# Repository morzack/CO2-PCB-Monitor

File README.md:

# CO2-PCB-Monitor

## v1

This repo contains the hardware and software required to manufacture and assemble a small seven segment CO2 monitor.

The monitor is built around a 4 digit seven segment display (with automatic dimming based on ambient light) that displays the current atmospheric CO2 concentration as measured by an Adafruit SCD-40 module over i2c.

In practice, this project can serve as a generic platform for any i2c module that might benefit from a 4 digit display. Potentially, other projects could be built around this architecture.

There is a BOM included: the total cost per unit, as of when it was made in early 2025, was ~90 USD.
Most of the cost comes from the SCD-40 module used -- directly integrating one of the modules onto the board should lower that price.

A rough block diagram is below:

The system has two power domains: a 5V domain is used for all digital logic, while the 3V domain is reserved for the seven-segement characters and associated dimming circuit.
This separation of power supplies was chosen to both allow for a soft startup sequence (putting less strain on the overall power supply), and to remove some voltage headroom for the LEDs.

The final design was manufactured using JLCPCB's services. A BOM is included with this repo, as well as manufacturing files.

The board can be programmed using the Arduino IDE and a separate ISP over the SPI lines.

## v2

Following the success of the first version, I want to make a few changes to ease manufacturing.
In particular, the design should shift to SMT where possible to enable JLCPCB PCBA.

The SPI and UART headers can be rethought as well to allow for future off-board additions.
There's value in making a port that an ESP32 or similar SoC can clip into for periodic recording over a network.

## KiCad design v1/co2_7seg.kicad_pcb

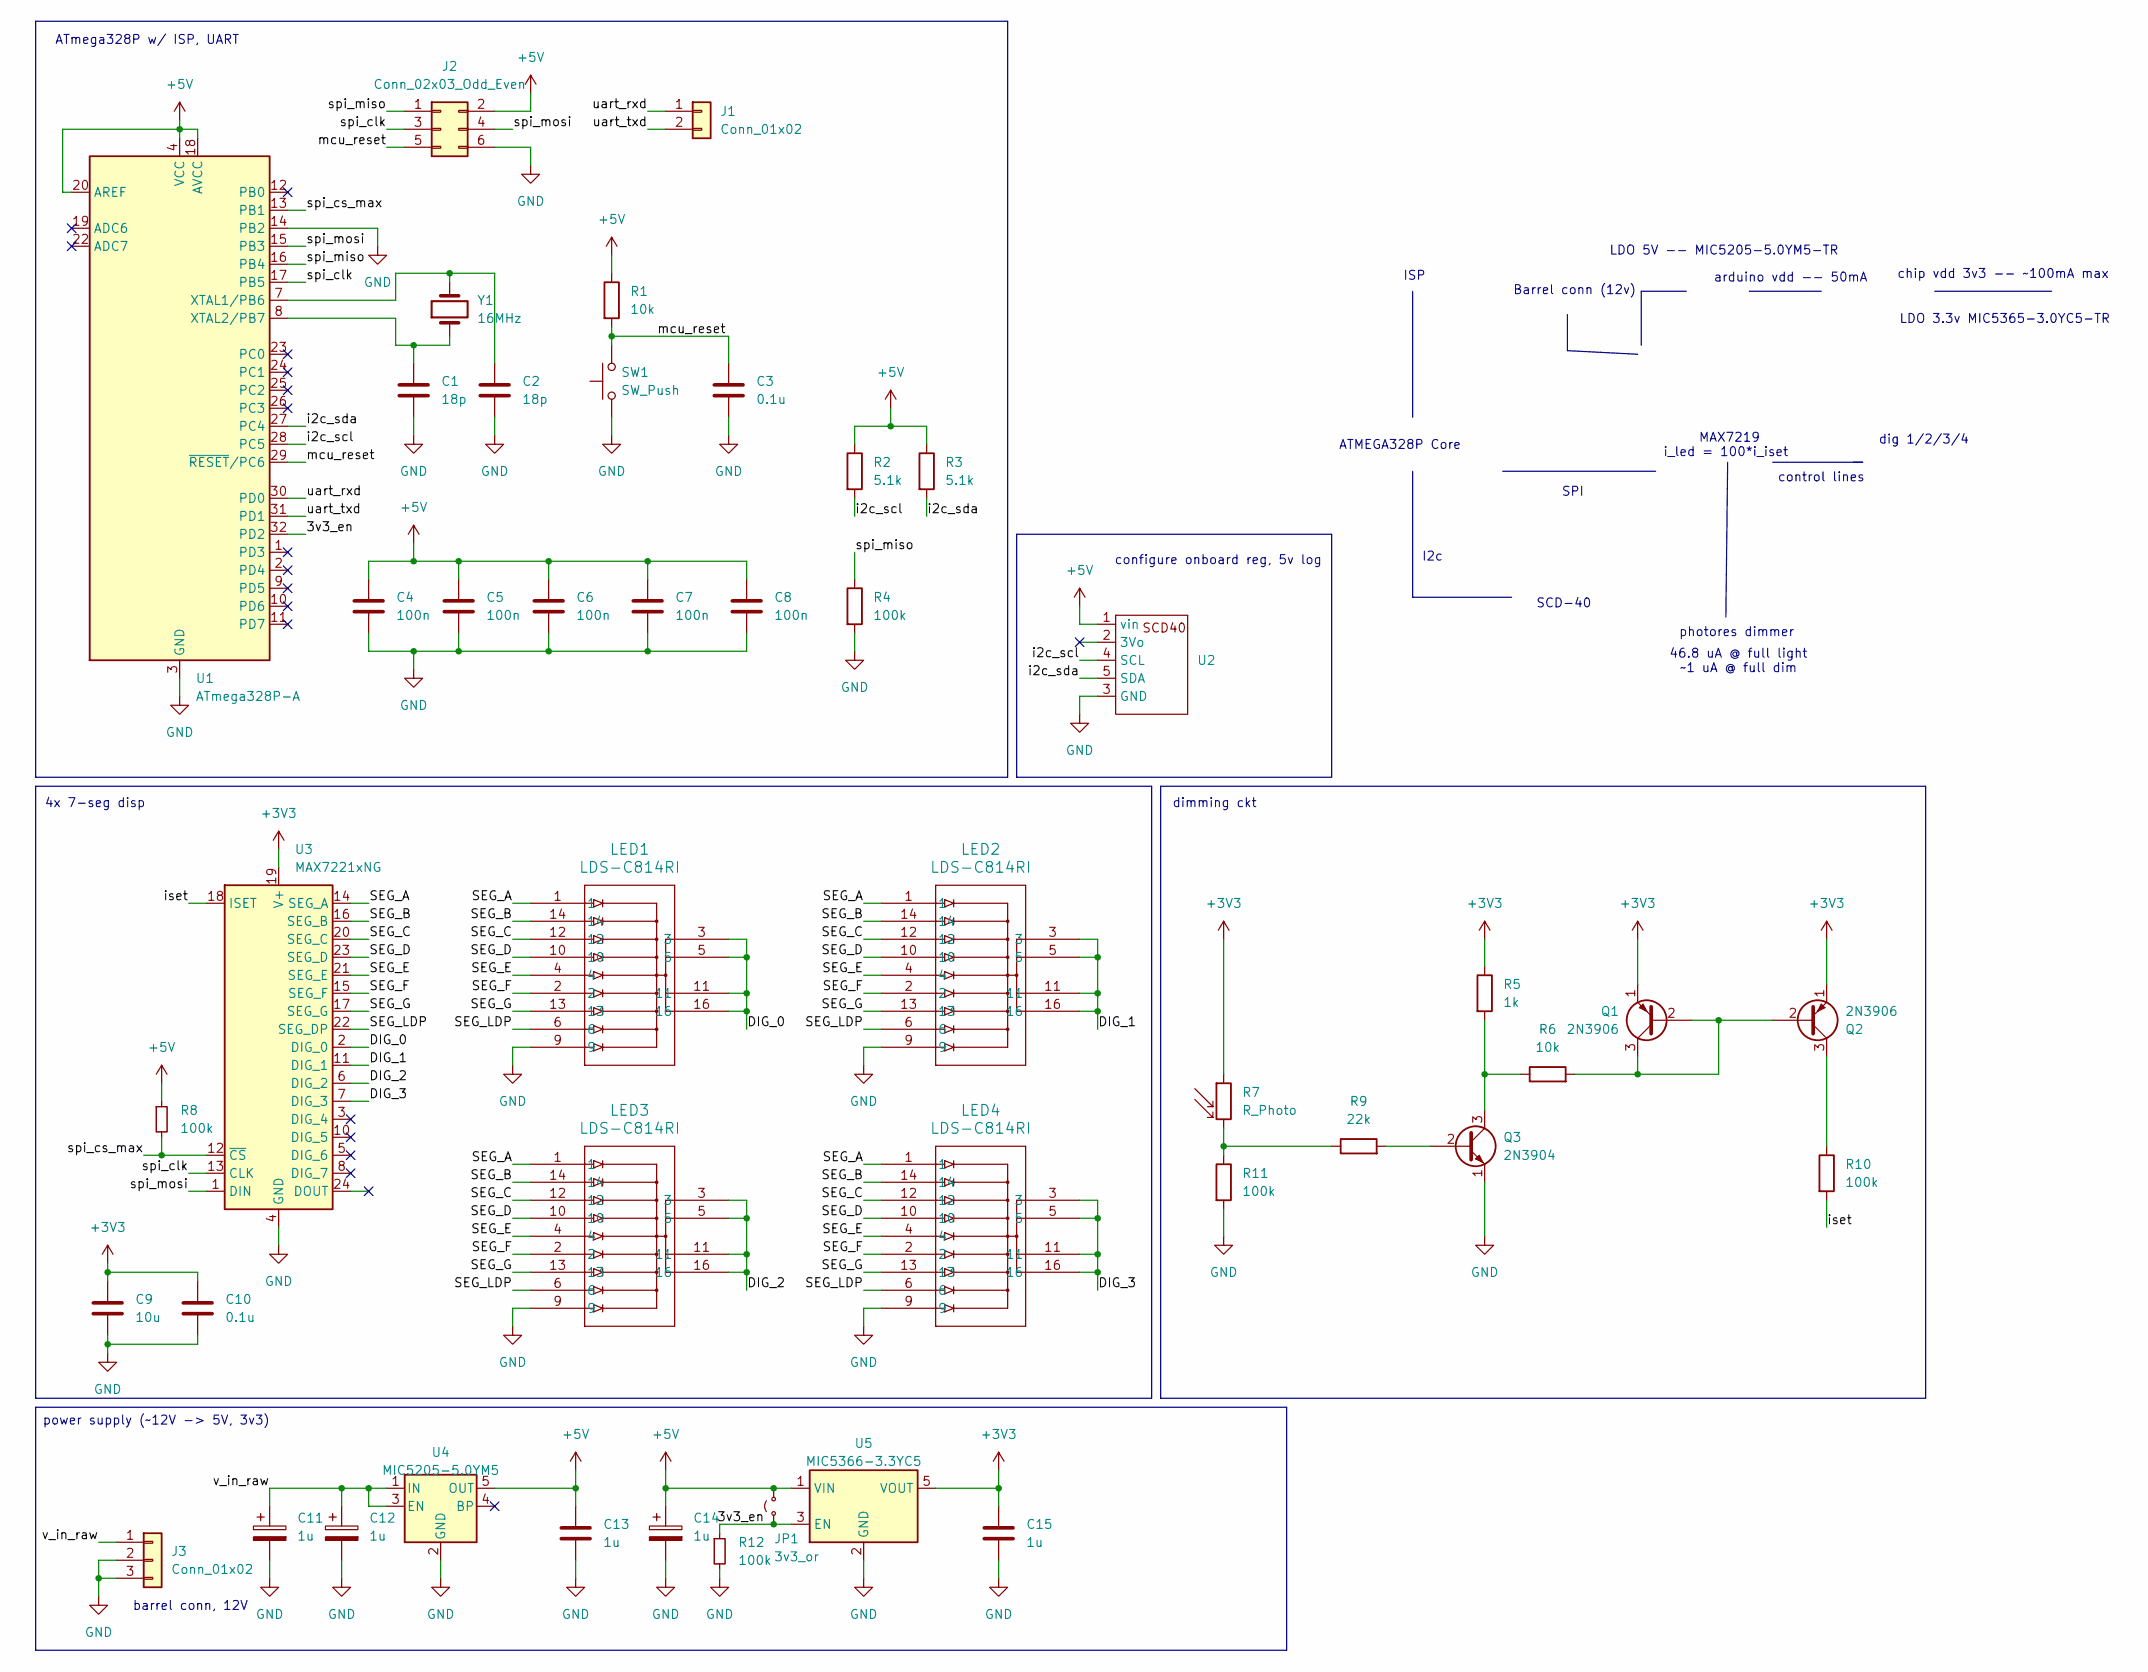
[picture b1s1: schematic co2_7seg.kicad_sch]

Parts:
C1, C2: 18p; C_0805_2012Metric_Pad1.18x1.45mm_HandSolder
C3, C10: 0.1u; C_0805_2012Metric_Pad1.18x1.45mm_HandSolder
C4, C5, C6, C7, C8: 100n; C_0805_2012Metric_Pad1.18x1.45mm_HandSolder
C9: 10u; C_0805_2012Metric_Pad1.18x1.45mm_HandSolder
C11, C12, C13, C14, C15: 1u; C_0805_2012Metric_Pad1.18x1.45mm_HandSolder
J1: Conn_01x02; PinHeader_1x02_P2.54mm_Vertical
J2: Conn_02x03_Odd_Even; PinHeader_2x03_P2.54mm_Vertical
J3: Conn_01x02; MPD_EJ508A
JP1: 3v3_or; SolderJumper-2_P1.3mm_Open_Pad1.0x1.5mm
LED1, LED2, LED3, LED4: LDS-C814RI; LDS-C814RI_LUM
Q1, Q2: 2N3906; TO-92_Inline
Q3: 2N3904; TO-92_Inline
R1, R6: 10k; R_0805_2012Metric_Pad1.20x1.40mm_HandSolder
R2, R3: 5.1k; R_0805_2012Metric_Pad1.20x1.40mm_HandSolder
R4, R8, R10, R11, R12: 100k; R_0805_2012Metric_Pad1.20x1.40mm_HandSolder
R5: 1k; R_0805_2012Metric_Pad1.20x1.40mm_HandSolder
R7: R_Photo; R_LDR_5.1x4.3mm_P3.4mm_Vertical
R9: 22k; R_0805_2012Metric_Pad1.20x1.40mm_HandSolder
SW1: SW_Push; SKQGADE010
U1: ATmega328P-A; TQFP-32_7x7mm_P0.8mm
U2: scd_40
U3: MAX7221xNG; DIP-24_W7.62mm_Socket
U4: MIC5205-5.0YM5; SOT-23-5
U5: MIC5366-3.3YC5; SOT-353_SC-70-5
Y1: 16MHz; XTAL_ECS-160-18-23A-EN-TR

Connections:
+3V3: C9.1, C10.1, C15.1, Q1.1 (E), Q2.1 (E), R5.1, R7.1, U3.19 (V+), U5.5 (VOUT)
+5V: C4.1, C5.1, C6.1, C7.1, C8.1, C13.1, C14.1, J2.2, JP1.2 (B), R1.1, R2.1, R3.1, R8.1, U1.4 (VCC), U1.6 (VCC), U1.18 (AVCC), U1.20 (AREF), U2.1 (vin), U4.5 (OUT), U5.1 (VIN)
/3v3_en: JP1.1 (A), R12.1, U1.32 (PD2), U5.3 (EN)
/DIG_0: LED1.3, LED1.5, LED1.11, LED1.16, U3.2 (DIG_0)
/DIG_1: LED2.3, LED2.5, LED2.11, LED2.16, U3.11 (DIG_1)
/DIG_2: LED3.3, LED3.5, LED3.11, LED3.16, U3.6 (DIG_2)
/DIG_3: LED4.3, LED4.5, LED4.11, LED4.16, U3.7 (DIG_3)
/SEG_A: LED1.1, LED2.1, LED3.1, LED4.1, U3.14 (SEG_A)
/SEG_B: LED1.14, LED2.14, LED3.14, LED4.14, U3.16 (SEG_B)
/SEG_C: LED1.12, LED2.12, LED3.12, LED4.12, U3.20 (SEG_C)
/SEG_D: LED1.10, LED2.10, LED3.10, LED4.10, U3.23 (SEG_D)
/SEG_E: LED1.4, LED2.4, LED3.4, LED4.4, U3.21 (SEG_E)
/SEG_F: LED1.2, LED2.2, LED3.2, LED4.2, U3.15 (SEG_F)
/SEG_G: LED1.13, LED2.13, LED3.13, LED4.13, U3.17 (SEG_G)
/SEG_LDP: LED1.6, LED2.6, LED3.6, LED4.6, U3.22 (SEG_DP)
/i2c_scl: R2.2, U1.28 (PC5), U2.4 (SCL)
/i2c_sda: R3.2, U1.27 (PC4), U2.5 (SDA)
/iset: R10.2, U3.18 (ISET)
/mcu_reset: C3.1, J2.5, R1.2, SW1.2, U1.29 (~RESET/PC6)
/spi_clk: J2.3, U1.17 (PB5), U3.13 (CLK)
/spi_cs_max: R8.2, U1.13 (PB1), U3.12 (~CS)
/spi_miso: J2.1, R4.1, U1.16 (PB4)
/spi_mosi: J2.4, U1.15 (PB3), U3.1 (DIN)
/uart_rxd: J1.1, U1.30 (PD0)
/uart_txd: J1.2, U1.31 (PD1)
/v_in_raw: C11.1, C12.1, J3.1, U4.1 (IN), U4.3 (EN)
GND: C1.2, C2.2, C3.2, C4.2, C5.2, C6.2, C7.2, C8.2, C9.2, C10.2, C11.2, C12.2, C13.2, C14.2, C15.2, J2.6, J3.2, J3.3, LED1.9, LED2.9, LED3.9, LED4.9, Q3.1 (E), R4.2, R11.2, R12.2, SW1.1, U1.3 (GND), U1.5 (GND), U1.14 (PB2), U1.21 (GND), U2.3 (GND), U3.4 (GND), U3.9 (GND), U4.2 (GND), U5.2 (GND)
unnamed: Q1.2 (B), Q1.3 (C), Q2.2 (B), R6.2
unnamed: Q2.3 (C), R10.1
unnamed: Q3.2 (B), R9.2
unnamed: Q3.3 (C), R5.2, R6.1
unnamed: R7.2, R9.1, R11.1
unnamed: C2.1, U1.7 (XTAL1/PB6), Y1.2
unnamed: C1.1, U1.8 (XTAL2/PB7), Y1.1

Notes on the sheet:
power supply (~12V -> 5V, 3v3)
i_led = 100*i_iset
I2c
control lines
4x 7-seg disp
dig 1/2/3/4
dimming ckt
barrel conn, 12V
LDO 3.3v MIC5365-3.0YC5-TR
46.8 uA @ full light ~1 uA @ full dim
ATMEGA328P Core
photores dimmer
Barrel conn (12v)
LDO 5V -- MIC5205-5.0YM5-TR
configure onboard reg, 5v log
SCD-40
chip vdd 3v3 -- ~100mA max
ATmega328P w/ ISP, UART
MAX7219
ISP
SPI
arduino vdd -- 50mA

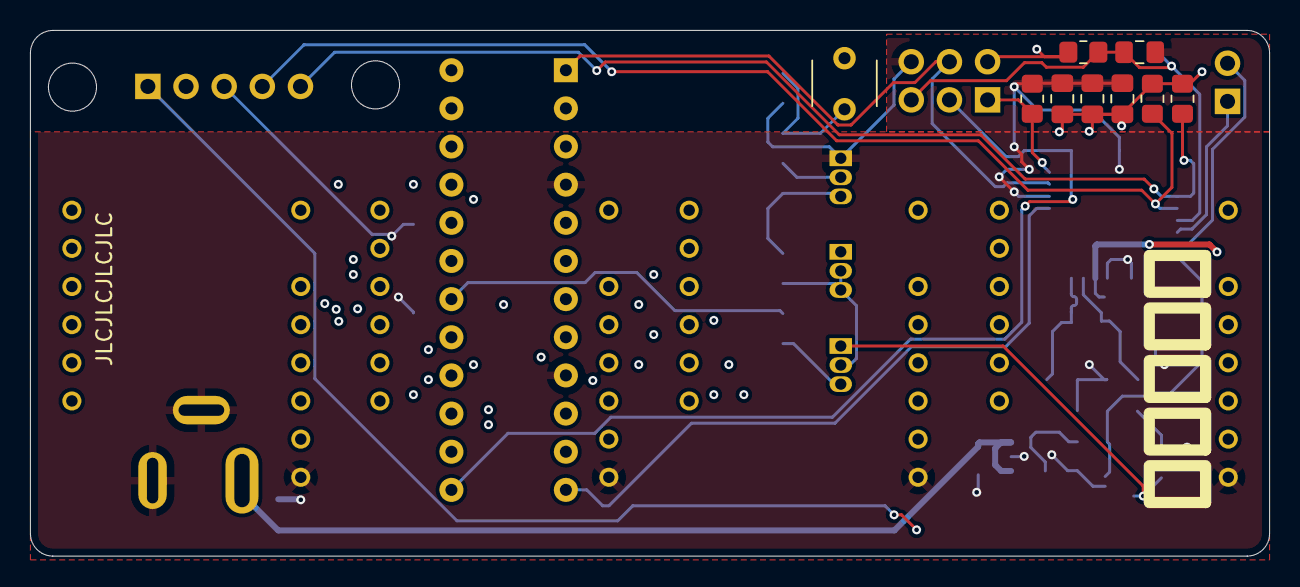
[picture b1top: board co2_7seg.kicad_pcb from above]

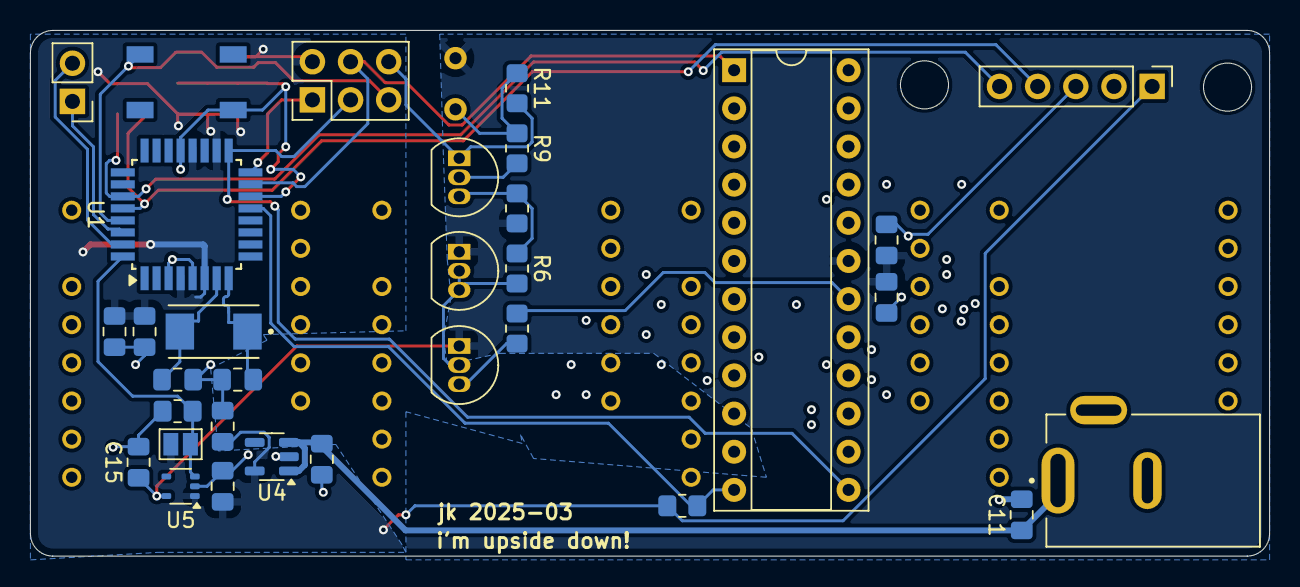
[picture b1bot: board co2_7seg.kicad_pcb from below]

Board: 4 copper layers, 82.5 x 35.0 mm, 45 parts (32 on the bottom side), 34 nets.

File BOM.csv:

Reference,Value,Datasheet,Footprint,Qty,DNP,stock_idx,Digikey,price per,
J2,Conn_02x03_Odd_Even,~,Connector_PinHeader_2.54mm:PinHeader_2x03_P2.54mm_Vertical,1,,1,,,
JP1,3v3_or,~,Jumper:SolderJumper-2_P1.3mm_Open_Pad1.0x1.5mm,1,,1,,,
C9,10u,~,Capacitor_SMD:C_0805_2012Metric_Pad1.18x1.45mm_HandSolder,1,,1,https://www.digikey.com/en/products/detail/samsung-electro-m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 ,0.08,0.08
"C3,C10",0.1u,~,Capacitor_SMD:C_0805_2012Metric_Pad1.18x1.45mm_HandSolder,2,,2,https://www.digikey.com/en/products/detail/yageo/CC0805KRX7R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,0.08,0.16
"C4,C5,C6,C7,C8",100n,~,Capacitor_SMD:C_0805_2012Metric_Pad1.18x1.45mm_HandSolder,5,,11,https://www.digikey.com/en/products/detail/samsung-electro-m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,0.1,0.5
U1,ATmega328P-A,http://ww1.microchip.com/downloads/en/DeviceDoc/ATmega328_P%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,Package_QFP:TQFP-32_7x7mm_P0.8mm,1,,25,https://www.digikey.com/en/products/detail/microchip-technol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,2.74,2.74
Y1,16MHz,~,inv_footprints:XTAL_ECS-160-18-23A-EN-TR,1,,28,https://www.digikey.com/en/products/detail/ecs-inc/ECS-160-1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,0.86,0.86
U2,~,,inv_footprints:scd_40,1,,34,https://www.digikey.com/en/products/detail/adafruit-industri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,44.95,44.95
Q3,2N3904,https://www.onsemi.com/pub/Collateral/2N3903-D.PDF,Package_TO_SOT_THT:TO-92_Inline,1,,36,https://www.digikey.com/en/products/detail/onsemi/2N3904BU/1413,0.28,0.28
R7,R_Photo,~,OptoDevice:R_LDR_5.1x4.3mm_P3.4mm_Vertical,1,,38,https://www.digikey.com/en/products/detail/advanced-photonix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,1.49,1.49
U3,MAX7221xNG,https://datasheets.maximintegrated.com/en/ds/MAX7219-MAX7221.pdf,Package_DIP:DIP-24_W7.62mm_Socket,1,,39,https://www.digikey.com/en/products/detail/analog-devices-in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,18.67,18.67
"Q1,Q2",2N3906,https://www.onsemi.com/pub/Collateral/2N3906-D.PDF,Package_TO_SOT_THT:TO-92_Inline,2,,40,https://www.digikey.com/en/products/detail/onsemi/2N3906BU/1414,0.27,0.54
SW1,SW_Push,~,inv_footprints:SKQGADE010,1,,44,https://www.digikey.com/en/products/detail/c-k/RS-187R05A2-D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,0.72,0.72
"LED1,LED2,LED3,LED4",LDS-C814RI,LDS-C814RI,inv_footprints:LDS-C814RI_LUM,4,,50,https://www.digikey.com/en/products/detail/lumex-opto-compon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,2.25,9
"R1,R6",10k,~,Resistor_SMD:R_0805_2012Metric_Pad1.20x1.40mm_HandSolder,2,,51,https://www.digikey.com/en/products/detail/yageo/RC0805FR-07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,0.14,0.28
"R4,R8,R10,R11,R12",100k,~,Resistor_SMD:R_0805_2012Metric_Pad1.20x1.40mm_HandSolder,5,,54,https://www.digikey.com/en/products/detail/yageo/RC0805FR-07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,0.1,0.5
R5,1k,~,Resistor_SMD:R_0805_2012Metric_Pad1.20x1.40mm_HandSolder,1,,56,https://www.digikey.com/en/products/detail/yageo/RC0805FR-07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,0.1,0.1
"R2,R3",5.1k,~,Resistor_SMD:R_0805_2012Metric_Pad1.20x1.40mm_HandSolder,2,,60,https://www.digikey.com/en/products/detail/panasonic-electro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,0.1,0.2
"C1,C2",18p,~,Capacitor_SMD:C_0805_2012Metric_Pad1.18x1.45mm_HandSolder,2,,64,https://www.digikey.com/en/products/detail/kemet/C0805C180M3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,0.1,0.2
R9,22k,~,Resistor_SMD:R_0805_2012Metric_Pad1.20x1.40mm_HandSolder,1,,65,https://www.digikey.com/en/products/detail/stackpole-electro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,0.1,0.1
U4,MIC5205-5.0YM5,http://ww1.microchip.com/downloads/en/DeviceDoc/20005785A.pdf,Package_TO_SOT_SMD:SOT-23-5,1,,66,https://www.digikey.com/en/products/detail/microchip-technol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 ,0.54,0.54
U5,MIC5366-3.3YC5,http://ww1.microchip.com/downloads/en/DeviceDoc/mic5365.pdf,Package_TO_SOT_SMD:SOT-353_SC-70-5,1,,67,https://www.digikey.com/en/products/detail/microchip-technol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 ,0.12,0.12
"C11,C12,C13,C14,C15",1u,~,Capacitor_SMD:C_0805_2012Metric_Pad1.18x1.45mm_HandSolder,5,,-- mixed values --,-- mixed values --,#N/A,#N/A
"J1,J3",Conn_01x02,~,-- mixed values --,2,,-- mixed values --,-- mixed values --,#N/A,#N/A
TOTAL,,,,,,,,,82.03

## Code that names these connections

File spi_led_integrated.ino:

#include <Arduino.h>
#include <SensirionI2CScd4x.h>
#include <Wire.h>

SensirionI2CScd4x scd4x;


// 11: MOSI/DIN
// 13: SCK/CLK
// 9: !CS (load)
// last 16 bits of serial data are latched on LOAD's rising edge

// to load data, take LOAD low, serially transmit the 16 bits of data, then set load high

// spi_clk -- PB5 = dig 13
// spi_mosi -- PB3 = dig 11
// spi_cs_max -- PB1 = dig 9
#define PIN_DIN 11
#define PIN_CLK 13
#define PIN_LOAD 9

#define PIN_EN_3V 2 // PD2 = dig 2

// #define PIN_DIN 11
// #define PIN_CLK 13
// #define PIN_LOAD 8

// #define PIN_CLK 6
// #define PIN_LOAD 5
// #define PIN_DIN 13

void send_bit(uint8_t bit);
void send_data_raw(uint16_t dat);
void write_reg(uint8_t reg, uint8_t dat);

#define CHAR_0 0x0
#define CHAR_1 0x1
#define CHAR_2 0x2
#define CHAR_3 0x3
#define CHAR_4 0x4
#define CHAR_5 0x5
#define CHAR_6 0x6
#define CHAR_7 0x7
#define CHAR_8 0x8
#define CHAR_9 0x9
#define CHAR_DASH 0xA
#define CHAR_E 0xB
#define CHAR_H 0xC
#define CHAR_L 0xD
#define CHAR_P 0xE
#define CHAR_BLANK 0xF

void write_digit(uint8_t digit, uint8_t character);

void make_co2_reading();
uint16_t last_co2;
float last_humid;
float last_temp;

void setup() {
  Wire.begin();
  uint16_t error;

  pinMode(PIN_DIN, OUTPUT);
  pinMode(PIN_CLK, OUTPUT);
  pinMode(PIN_LOAD, OUTPUT);
  pinMode(PIN_EN_3V, OUTPUT);

  digitalWrite(PIN_DIN, LOW);
  digitalWrite(PIN_CLK, LOW);
  digitalWrite(PIN_LOAD, HIGH);
  digitalWrite(PIN_EN_3V, LOW);

  // soft bringup the max chip
  delay(1000);
  digitalWrite(PIN_EN_3V, HIGH);
  delay(2000);

  // turn on only digit 0
  write_reg(0x9, 0xFF); // decode mode: 
  write_reg(0xA, 0x0F); // intensity
  write_reg(0xB, 0x03); // 0x3 for 4 digits
  write_reg(0xC, 0x01); // shutdown

  delay(1000);

  // bring up co2 sense
  scd4x.begin(Wire);
  error = scd4x.stopPeriodicMeasurement();
  error = scd4x.startLowPowerPeriodicMeasurement();

  write_num(0);
}

void loop() {
  // cycle through test digits
  // uint8_t x = 0;
  // while (x <= 9) {    
  //   write_digit(0, x);

  //   if (x == 9) {
  //     x = 0;
  //   }
  //   x++;

  //   delay(1000);
  // }

  // uint16_t a = 0;
  // uint16_t inc = 59;
  // while (a <= 9999) {
  //   write_num(a);
  //   if (a > 9999) {
  //     a %= 9999;
  //   }
  //   else {
  //     a += inc;
  //   }
  //   delay(250);
  // }

  make_co2_reading();
  write_num(last_co2);

  unsigned long startMillis = millis();
  while (millis() - startMillis < (1000UL * 60UL * 5UL)); // wait 5m between readings
}


void make_co2_reading() {
  bool is_data_ready = false;
  uint16_t err = scd4x.getDataReadyFlag(is_data_ready);
  if (err) {
    return;
  }

  if (!is_data_ready) {
    return;
  }

  uint16_t tmp_co2;
  err = scd4x.readMeasurement(tmp_co2, last_temp, last_humid);
  if (err) {
    return;
  }

  if (tmp_co2 != 0) {
    last_co2 = tmp_co2;
  }
}

void send_bit(uint8_t bit) {
  // bring data to value
  digitalWrite(PIN_DIN, bit == 0 ? LOW : HIGH);
  // wait a bit
  delay(1); // 1
  // bring clock high to latch value
  digitalWrite(PIN_CLK, HIGH);
  delay(1); // 3
  
  // bring clock low/hold, prep for next
  digitalWrite(PIN_CLK, LOW);
  delay(1); // 4
}

void send_data_raw(uint16_t dat) {
  digitalWrite(PIN_CLK, LOW);
  digitalWrite(PIN_LOAD, LOW);
  digitalWrite(PIN_DIN, LOW);
  delay(1); // 50
  for (uint8_t i=0; i<16; i++) {
    uint8_t b = (dat>>(15-i)) & 0x01;
    send_bit(b);
  }
  digitalWrite(PIN_LOAD, HIGH);
  digitalWrite(PIN_CLK, LOW);
  digitalWrite(PIN_DIN, LOW);
}

void write_reg(uint8_t reg, uint8_t dat) {
  uint16_t sending = 0x00;
  sending |= dat;
  sending |= (reg << 8);
  send_data_raw(sending);
}

void write_digit(uint8_t digit, uint8_t character) {
  // assume digit is zero-indexed
  write_reg(digit+1, character);
}

void write_num(uint16_t num) {
  uint8_t a = num % 10;
  uint8_t b = (num/10) % 10;
  uint8_t c = (num/100) % 10;
  uint8_t d = (num/1000) % 10;
  write_digit(3, a);
  write_digit(2, b);
  write_digit(1, c);
  write_digit(0, d);
}

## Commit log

2025-05-13 Update LICENSE
2025-05-13 Add KiCad + src project files
    TODO make new repo for shared symbols, update path + add as submodule
2025-05-13 update code location for IDE
2025-05-13 add reference to footprint libs, add BOM
2025-05-13 update kicad schematic to include digikey link(s)
2025-12-14 move project structure
2025-12-16 update v2 schem
